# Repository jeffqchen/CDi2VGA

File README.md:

# HD15 Port Add-on for Phlips CD-i

## Introduction

The Philips CD-i can be modded with RGB output. However the actual output port sometimes involve cutting big holes or removing the Composite Video jack to fit. Therefore, I have come up this addon to fit an HD15 port onto the grills on the back of the console.

## Pin Definition

The pin definition follows the standard of my [VGA Dongle Series](https://github.com/jeffqchen/Console-VGA-Dongle-Series), which carries RGBS plus stereo audio.

- Pin 1-3: RGB signals
- Pin 13: HSync/CSync (connect to `CS-TTL` or `CS-75`)
- Pin 14: VSync (normally unpopulated)
- Pin 5, 6-8, 10: Ground
- Pin 12 & 15: Audio L & R
- Pin 9: Fused 5V

## Compatibility

This VGA signal is compatible with all major scalers.
- RetroTINK 5X - with my [dock](https://github.com/jeffqchen/RetroTINK-5X-SCART-Dock)
- RetroTINK 4K - directly connect to the `HD15` port or through my [SCART2VGA adapter](https://github.com/jeffqchen/RetroTINK-4K-SCART2VGA-Adapter)
- OSSC - directly connect to AV3 (VGA) port **IF** `CS_TTL` is connected to `Pin 13`
- GBSControl

## Currently supported Models
- CD-i 450 & 550 - [Guide](./450%20%26%20550/README.md)

-----------

Shield: [![CC BY-SA 4.0][cc-by-sa-shield]][cc-by-sa]

This work is licensed under a
[Creative Commons Attribution-ShareAlike 4.0 International License][cc-by-sa].

[![CC BY-SA 4.0][cc-by-sa-image]][cc-by-sa]

[cc-by-sa]: http://creativecommons.org/licenses/by-sa/4.0/
[cc-by-sa-image]: https://licensebuttons.net/l/by-sa/4.0/88x31.png
[cc-by-sa-shield]: https://img.shields.io/badge/License-CC%20BY--SA%204.0-lightgrey.svg

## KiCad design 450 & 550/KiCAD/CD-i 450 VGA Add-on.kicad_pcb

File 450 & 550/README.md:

# Building Guide for Philips CD-i 450 & 550

## Introduction

This variant fits the CD-i 450 & 550, since both share the same chassis and motherboard design. It utilizes a section of rear vents, and require two holes drilled on the bottom of the casing for installation. The final result is slick and does not require cutting additional holes or removing the Composite Video jack.

Since the original Composite Video jack is preserved, it is possible to output both CVBS and RGBS at the same time.

## Parts

- 3D Printed parts - [STL Files](./3D%20Print)
- PCB - [Gerber File](./KiCAD/jlcpcb/gerber/CD-i%20450%20VGA%20Add-on.zip)
- VGA Port Slim, Female - [Link](https://github.com/jeffqchen/JeffParts/blob/main/Connectors/HD15/Slim/Female%20PCB/info.md)
- (Optional) Resistors, imperial 0603
  - R1: 0 Ohm, for fusing the 5V power line
  - R2: 1M Ohm, for connecting the VGA cable shielding to ground with ESD protection
- M2/M3 screw and hex nut - [Link](https://github.com/jeffqchen/JeffParts/blob/main/Parts/M2%20M3%20Hex%20Screw%20%26%20Nut/info.md)
  - 2x M3x8 screws
  - 2x M3x16 screws
  - 4x M3 nuts
- Colored wire at around 15cm

## Drilling The Chassis

Assembly the 3D printed pieces together with screw and nuts, put it in place and use the two holes on the bottom as a guide to drill. The size of the bit should be 3mm / 1/8".

Fit a piece of wood on the inside of the metal shielding for taking the pressure of the drill. Make sure to drill through both the plastic and the metal shielding.

After the holes are drilled, remove the 3D printed shell and disassemble it for the next step.

## PCB & Shell Assembly

There is nothing special about the soldering.

Resistor R1 and R2 are optional if you have requirements for 5V power or ESD consideration.

Make sure the VGA port is soldered on properly with no gap between the base of the port and the PCB.

Signals are marked on the PCB. Use colored wires of your choice to help with later installation.

Finally, install the PCB assembly into the 3D printed shell with M3x16mm screws and nuts.

## Installation

Thread the wires from the various vents into the metal shielding.

Note the first and last vent are used by the shell and should not have wires going through them. 

On the inside, I mainly used the top row holes since the lower ones might interfere with the motherboard.

Make sure the wires are not played with or bent too much during this step, as they tend to break at the solder joint.

After threading all the wires, carefully close the port assembly onto the back of the plastic chassis.

Insert two M3x8mm screws from the bottom of the console.

Use two M3 nuts to secure the screws and the assembly.

Before installing the motherboard back into the chassis, cut the 4 protruding capacitor leads from under the board to make sure they would not touch the newly installed nuts.

Install the motherboard and make sure all the wires are accounted for.

## Finalizing

Here is an example of my own RGB mod install. I trimmed the wires to better fit them on the inside of the console.

When closing down the top metal shielding, make sure to check if any wire is being crushed by the edge of the top shielding (mine was fine.)

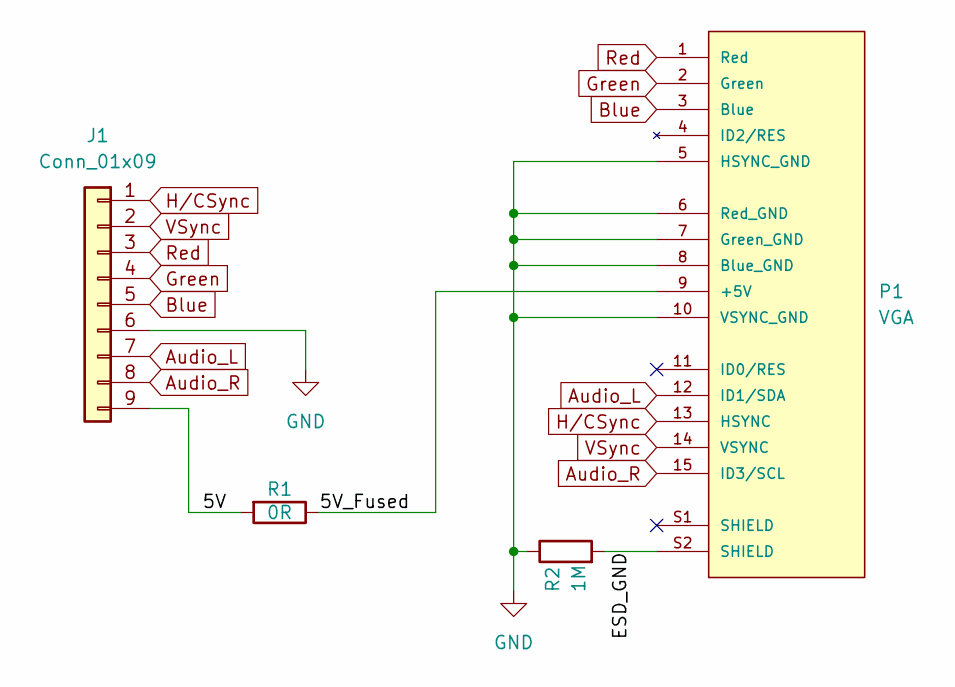
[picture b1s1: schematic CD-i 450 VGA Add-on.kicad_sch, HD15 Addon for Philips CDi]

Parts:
J1: Conn_01x09; PinHeader_1x09_P2.54mm_Vertical
P1: VGA; VGA_female_rightangle_slim; PARTREV N/A
R1: 0R; R_0603_1608Metric_Pad0.98x0.95mm_HandSolder
R2: 1M; R_0603_1608Metric_Pad0.98x0.95mm_HandSolder

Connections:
/5V: J1.9, R1.2
/5V_Fused: P1.9 (+5V), R1.1
/ESD_GND: P1.S2 (SHIELD), R2.2
Audio_L: J1.7, P1.12 (ID1/SDA)
Audio_R: J1.8, P1.15 (ID3/SCL)
Blue: J1.5, P1.3 (Blue)
GND: J1.6, P1.5 (HSYNC_GND), P1.6 (Red_GND), P1.7 (Green_GND), P1.8 (Blue_GND), P1.10 (VSYNC_GND), R2.1
Green: J1.4, P1.2 (Green)
H/CSync: J1.1, P1.13 (HSYNC)
Red: J1.3, P1.1 (Red)
VSync: J1.2, P1.14 (VSYNC)

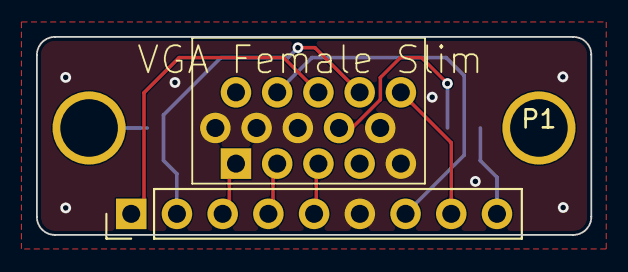
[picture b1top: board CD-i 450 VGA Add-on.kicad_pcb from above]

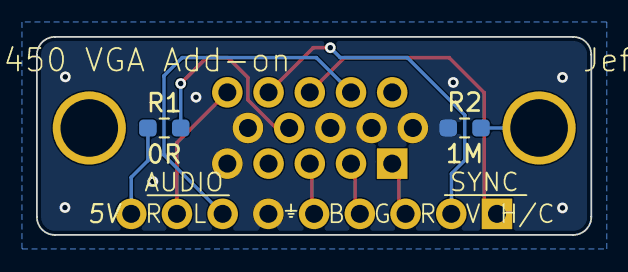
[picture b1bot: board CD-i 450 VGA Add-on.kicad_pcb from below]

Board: 2 copper layers, 30.8 x 11.0 mm, 4 parts (2 on the bottom side), 11 nets.
